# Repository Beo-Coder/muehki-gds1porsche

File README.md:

# Porsche Mü(h)k

### Raspberry Pi Pico powered HID joystick for an old Porsche tractor

# Table of Contents
1. [Features](#features)
2. [Description](#description)
3. [Pinout](#pinout)
4. [Settings](#settings)
   1. [Load Preset](#load-preset)
   2. [Save Preset](#save-preset)
   3. [Modify Preset](#modify-preset)
      1. [General Settings](#general-settings)
      2. [Axes Settings](#axes-settings)
      3. [Button Settings](#button-settings)
  
   4. [Reinit Joystick](#reinit-joystick)
   5. [Reset Preset](#reset-preset)
   6. [Factory Reset](#factory-reset)
   7. [Disable Output](#disable-output)
5. [Notes](#notes)

# Features

- upto 8 analog axes
- upto 24 digital buttons
- fully customizable axes control curves
- fully customizable button behavior
- 10 different config presets
- easy control over rotary controller and LCD
- acts as gamepad or keyboard
- expandable 

# Description

Porsche Mü(h)k is a Raspberry Pi Pico powered controller
to emulate a HI-Device to control various games by using real actuators such as steering wheel,
gas and break pedal of a real tractor/car.
Various actuators can be connected either as analog or digital sensors, like potentiometers and buttons.
It can emulate a gamepad/joystick or a keyboard, depending on which mode is desired.
Each analog axis can operate in one of four different modes, giving full control over the behavior of the axis.

**It may be useful to use an emulator on the host PC to further configure the axes and buttons.**
# Usage

1. Connect all analog and digital actuators according to the pinout guide
2. Connect the Pico to a computer/laptop
3. Load/modify a preset
4. Have fun!

# Pinout

**Note**  
0 = Axis/Button 0 in software.  
If an axis/button is connected to port 2, but in software only two axes/buttons are selected,
the input is not sampled and has no output.

### Analog Headers

<pre> 
            +-----------+
+-----------+-----------+-----------+
|           |           |           |
|     A     |    GND    |    Vcc    |
|           |           |           |
+-----------+-----------+-----------+
</pre>

- A = Analog Input  
- GND = GND
- Vcc = Vcc (3.3V)  

### Digital Headers
<pre>
      +-----------+
+-----------+-----------+
|           |           |
|     S1    |    S2     |
|           |           |
+-----------+-----------+
</pre>

- S1 = Button contact 1
- S2 = Button contact 2

The Button must close or open these two connections.

**More detailed pinout in hardwareReadme**

# Settings

## Load Preset

1. Go to /Settings/Set Preset
2. Select desired preset
3. The Device will reset automatically

## Save Preset

1. Go to /Settings/Save Preset
2. Select desired preset
3. The config is saved to the preset

## Modify Preset

### General Settings
Menu: /Settings/General

- Number of Axes: Select the number of analog inputs/axes (0–8).
- Number of Buttons: Select the number of digital inputs/buttons (0–24).
- Digital Axis Mode: Set the mode for all axes
  - Analog: Axes will be emulated as analog axes (joystick)
  - Analog/Digital: Axes will be emulated as buttons on a joystick (only digital axes)
  - Keyboard: Axes and buttons will be emulated as a keyboard

On Analog/Digital and Keyboard mode, each axis will get two buttons/digital outputs assigned. 
One for an upper limit, one for a lower limit.
In these modes, an axis has only three states: center/off, upper limit, lower limit.

**Important:** After any change of these settings, you have to save the preset and restart the device! [Save Settings](#save-preset), [Reinit Joystick](#reinit-joystick)

### Axes Settings
Menu: /Settings/Axes/{*number of axis*}

- Calibrate: Calibrates the axis
- Base set: Sets the base of the control curve (only in exponential and logarithmic mode)
- Mode: Sets the mode of the axis (linear, exponential, logarithmic, digital)
- Digital Calibration: Calibration for digital mode

#### Calibration
It will calibrate your axis settings.  
Set the minimum position of the axis, this is the position where the output of the axis is the smallest.
Same with the maximum.  
If the center position is not calibrated, the center position is automatically set to the midpoint between minimum and maximum.
If the center is calibrated, one half of the calibration curve can be shorter/longer than the other.

#### Modes
- linear: The curve of the output is linear to the input
- exponential/logarithmic: The curve of the output is exponential/logarithmic to the input (based on base)
- digital: The axis has three states (center/off, upper limit, lower limit) in the general "Analog" mode these will be represented as an analog axis which is either 0, maximum or minimum.

#### Base set
In exponential and logarithmic mode, the base will set the curvature/steepness of the output curve.  
The output curve is split in two halves (base 0 and base 1).
Each base can be set separately, or both bases can be set to the same value.  
Base 0 is the base for the curve between minimum and the center, base 1 for the middle between maximum.  
For exponential curves the value should be greater than 0, for logarithmic curves the value should be smaller than 0.  
If the value is 0, it is linear.  
See also the diagrams below.

#### Digital Calibration
This will select the digital lower and upper limit of the axis.  
Set the position after which the lower/upper output/button should be pressed/set to minimum/maximum.  
All input values that are smaller/greater than the limit will result in the minimum/maximum output value.  
If the input value is between the boarder, no button is pressed (in (general) Analog/Digital or Keyboard mode) or the axis will be 0/center position ((general) Analog Mode).

#### Diagrams
The x-axis represents the input value.
- 0 = center (input) position
- -10 = minimum (input) position
- 10 = maximum (input) position

All of these values can be calibrated with axis calibration.

The y-axis represents the output value (analog mode only)
- 0 = center/0 output
- -10 = minimum (output) value
- 10 = maximum (output) value

Base 0 is the base for the curve between minimum and the center, base 1 for the middle between maximum.

These values will can't be directly controlled.

##### Linear curves:

| Linear axis curve without center calibration                                                                      | Linear axis curve with (different) center calibration                                                                | Linear axis curve with (different) center calibration, different minimum calibration                                      |
|-------------------------------------------------------------------------------------------------------------------|----------------------------------------------------------------------------------------------------------------------|---------------------------------------------------------------------------------------------------------------------------|
|  |  |  |

##### Exponential curves:
| Exponential axis curve without center calibration, same bases                                                          | Exponential axis curve without center calibration, different bases                                                        | Exponential axis curve with (different) center calibration, different bases                                                   |
|------------------------------------------------------------------------------------------------------------------------|---------------------------------------------------------------------------------------------------------------------------|-------------------------------------------------------------------------------------------------------------------------------|
|  |  |  |

##### Logarithmic curves:
| Logarithmic axis curve without center calibration, same bases                                                       | Logarithmic axis curve without center calibration, different bases                                                     | Logarithmic axis curve with (different) center calibration, different bases                                                |
|---------------------------------------------------------------------------------------------------------------------|------------------------------------------------------------------------------------------------------------------------|----------------------------------------------------------------------------------------------------------------------------|
|  |  |  |

##### Other curves (Combinations of all) :
| Exponential half with other half linear (without center calibration)                                                                                 | Exponential half with other half linear, (different) center calibration                                                                                       | Logarithmic half with other half exponential, (different) center calibration                                                                         |
|------------------------------------------------------------------------------------------------------------------------------------------------------|---------------------------------------------------------------------------------------------------------------------------------------------------------------|------------------------------------------------------------------------------------------------------------------------------------------------------|
|  |  |  |

**Note:**
There are many other ways to adjust the curves. See also the Desmos calculator: [Desmos calculator](https://www.desmos.com/calculator/y6jawpiyea)  
Note that the values of the Desmos calculator do not match those of the device.

### Button Settings

Menu: /Settings/Buttons/{*number of button*}

- Mode: Whether the button should behave as (temporary) button or as (toggle) button
- Type: Whether the button is NO (normally open) or NC (normally closed)

#### Mode
- Button: Button behaves as a button. There is only an output when the button is pressed.
- Toggle: Button behaves as a toggle button. Ont the first press the output goes high/1, the next press sets the output to 0/low.

#### Type
- Normally Open
- Normally Closed

Whether the button opens or closes on a press.

**Important:**
Axes and button settings are adapted immediately.
To keep them after the joystick is reloaded or turned off the settings must be saved. [Save Settings](#save-preset)  
There is no need to reinit the joystick after axes or button settings have changed.

## Reinit Joystick

This option reloads the joystick. 
All settings that are not saved will be lost.

## Reset Preset

The current selected preset will be set to factory settings.
After that, the joystick will be reloaded.

## Factory Reset

All settings (all presets) are set back to factory settings.
After that, the joystick will be reloaded.

## Disable Output
This setting disables the output of the computer.  
Especially useful in Keyboard mode.  
Press it again to enable the output again.

# Notes
The configuration/device can be tested on gamepad/joystick test websites/software.  
Example website I used for testing: [Gamepad tester](https://hardwaretester.com/gamepad)

More detailed hardware/software guides are under [READMEhardware](READMEhardware.md)/[READMEsoftware](READMEsoftware.md)  
There are also the board dimensions as well as the schematic/gerber files.

There are no settings stored on the Pico. So the Pico can also be used for other projects.

If there are any bugs/problems, or you have any questions, please contact me.

Mühk or Mük is are the same things. :)

( ._.)

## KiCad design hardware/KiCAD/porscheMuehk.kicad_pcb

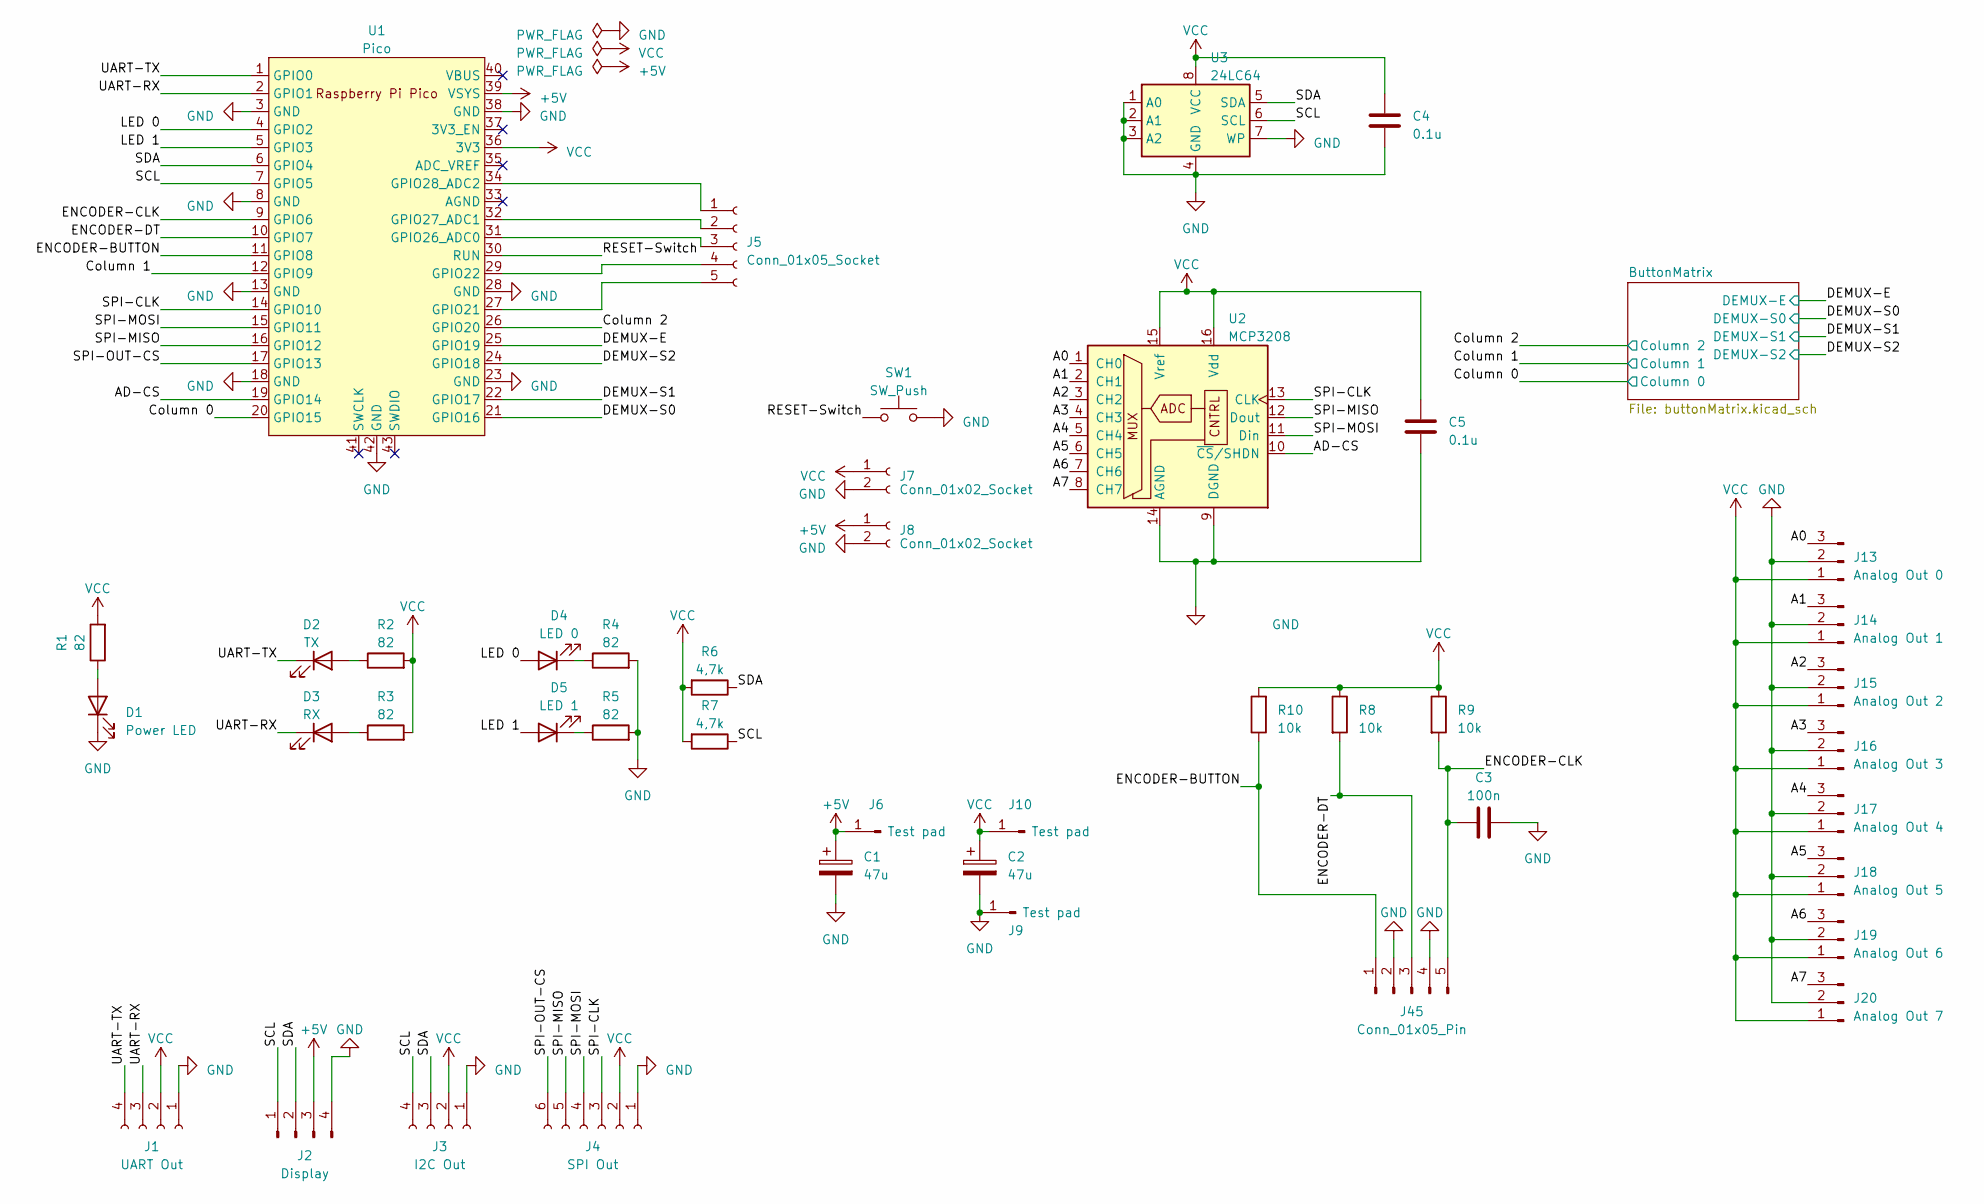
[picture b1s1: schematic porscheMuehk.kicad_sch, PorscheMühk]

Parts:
C1, C2: 47u; CP_Elec_5x5.3
C3: 100n; C_0805_2012Metric_Pad1.18x1.45mm_HandSolder
C4, C5: 0.1u; C_0805_2012Metric_Pad1.18x1.45mm_HandSolder
D1: Power LED; LED_0805_2012Metric_Pad1.15x1.40mm_HandSolder
D2: TX; LED_0805_2012Metric_Pad1.15x1.40mm_HandSolder
D3: RX; LED_0805_2012Metric_Pad1.15x1.40mm_HandSolder
D4: LED 0; LED_0805_2012Metric_Pad1.15x1.40mm_HandSolder
D5: LED 1; LED_0805_2012Metric_Pad1.15x1.40mm_HandSolder
J1: UART Out; PinSocket_1x04_P2.54mm_Vertical
J2: Display; Molex_KK-254_AE-6410-04A_1x04_P2.54mm_Vertical
J3: I2C Out; PinSocket_1x04_P2.54mm_Vertical
J4: SPI Out; PinSocket_1x06_P2.54mm_Vertical
J5: Conn_01x05_Socket; PinSocket_1x05_P2.54mm_Vertical
J6, J9, J10: Test pad; TestPoint_Pad_1.5x1.5mm
J7, J8: Conn_01x02_Socket; PinSocket_1x02_P2.54mm_Vertical
J13: Analog Out 0; Molex_KK-254_AE-6410-03A_1x03_P2.54mm_Vertical
J14: Analog Out 1; Molex_KK-254_AE-6410-03A_1x03_P2.54mm_Vertical
J15: Analog Out 2; Molex_KK-254_AE-6410-03A_1x03_P2.54mm_Vertical
J16: Analog Out 3; Molex_KK-254_AE-6410-03A_1x03_P2.54mm_Vertical
J17: Analog Out 4; Molex_KK-254_AE-6410-03A_1x03_P2.54mm_Vertical
J18: Analog Out 5; Molex_KK-254_AE-6410-03A_1x03_P2.54mm_Vertical
J19: Analog Out 6; Molex_KK-254_AE-6410-03A_1x03_P2.54mm_Vertical
J20: Analog Out 7; Molex_KK-254_AE-6410-03A_1x03_P2.54mm_Vertical
J45: Conn_01x05_Pin; Molex_KK-254_AE-6410-05A_1x05_P2.54mm_Vertical
R1, R2, R3, R4, R5: 82; R_0805_2012Metric_Pad1.20x1.40mm_HandSolder
R6, R7: 4,7k; R_0805_2012Metric_Pad1.20x1.40mm_HandSolder
R8, R9, R10: 10k; R_0805_2012Metric_Pad1.20x1.40mm_HandSolder
SW1: SW_Push; SW_Push_1P1T_NO_6x6mm_H9.5mm
U1: Pico; RPi_Pico_SMD_TH
U2: MCP3208; SOIC-16_3.9x9.9mm_P1.27mm
U3: 24LC64; SOIC-8_3.9x4.9mm_P1.27mm

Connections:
+5V: C1.1, J2.3, J6.1, J8.1, U1.39 (VSYS)
/A0: J13.3, U2.1 (CH0)
/A1: J14.3, U2.2 (CH1)
/A2: J15.3, U2.3 (CH2)
/A3: J16.3, U2.4 (CH3)
/A4: J17.3, U2.5 (CH4)
/A5: J18.3, U2.6 (CH5)
/A6: J19.3, U2.7 (CH6)
/A7: J20.3, U2.8 (CH7)
/AD-CS: U1.19 (GPIO14), U2.10 (~CS/SHDN)
/Column 0: U1.20 (GPIO15); also elsewhere on the board
/Column 1: U1.12 (GPIO9); also elsewhere on the board
/Column 2: U1.26 (GPIO20); also elsewhere on the board
/DEMUX-E: U1.25 (GPIO19); also elsewhere on the board
/DEMUX-S0: U1.21 (GPIO16); also elsewhere on the board
/DEMUX-S1: U1.22 (GPIO17); also elsewhere on the board
/DEMUX-S2: U1.24 (GPIO18); also elsewhere on the board
/ENCODER-BUTTON: J45.1, R10.1, U1.11 (GPIO8)
/ENCODER-DT: J45.3, R8.2, U1.10 (GPIO7)
/LED 0: D4.2 (A), U1.4 (GPIO2)
/LED 1: D5.2 (A), U1.5 (GPIO3)
/RESET-Switch: SW1.1, U1.30 (RUN)
/SCL: J2.1, J3.4, R7.1, U1.7 (GPIO5), U3.6 (SCL)
/SDA: J2.2, J3.3, R6.1, U1.6 (GPIO4), U3.5 (SDA)
/SPI-CLK: J4.3, U1.14 (GPIO10), U2.13 (CLK)
/SPI-MISO: J4.5, U1.16 (GPIO12), U2.12 (Dout)
/SPI-MOSI: J4.4, U1.15 (GPIO11), U2.11 (Din)
/SPI-OUT-CS: J4.6, U1.17 (GPIO13)
/UART-RX: D3.1 (K), J1.3, U1.2 (GPIO1)
/UART-TX: D2.1 (K), J1.4, U1.1 (GPIO0)
unnamed: D1.2 (A), R1.1
unnamed: D2.2 (A), R2.1
unnamed: D3.2 (A), R3.1
unnamed: D4.1 (K), R4.1
unnamed: D5.1 (K), R5.1
unnamed: J5.1, U1.34 (GPIO28_ADC2)
unnamed: J5.2, U1.32 (GPIO27_ADC1)
unnamed: J5.3, U1.31 (GPIO26_ADC0)
unnamed: J5.4, U1.29 (GPIO22)
unnamed: J5.5, U1.27 (GPIO21)
VCC: C2.1, C4.1, C5.1, J1.2, J3.2, J4.2, J7.1, J10.1, J13.1, J14.1, J15.1, J16.1, J17.1, J18.1, J19.1, J20.1, R1.2, R2.2, R3.2, R6.2, R7.2, R8.1, R9.1, R10.2, U1.36 (3V3), U2.15 (Vref), U2.16 (Vdd), U3.8 (VCC); also elsewhere on the board

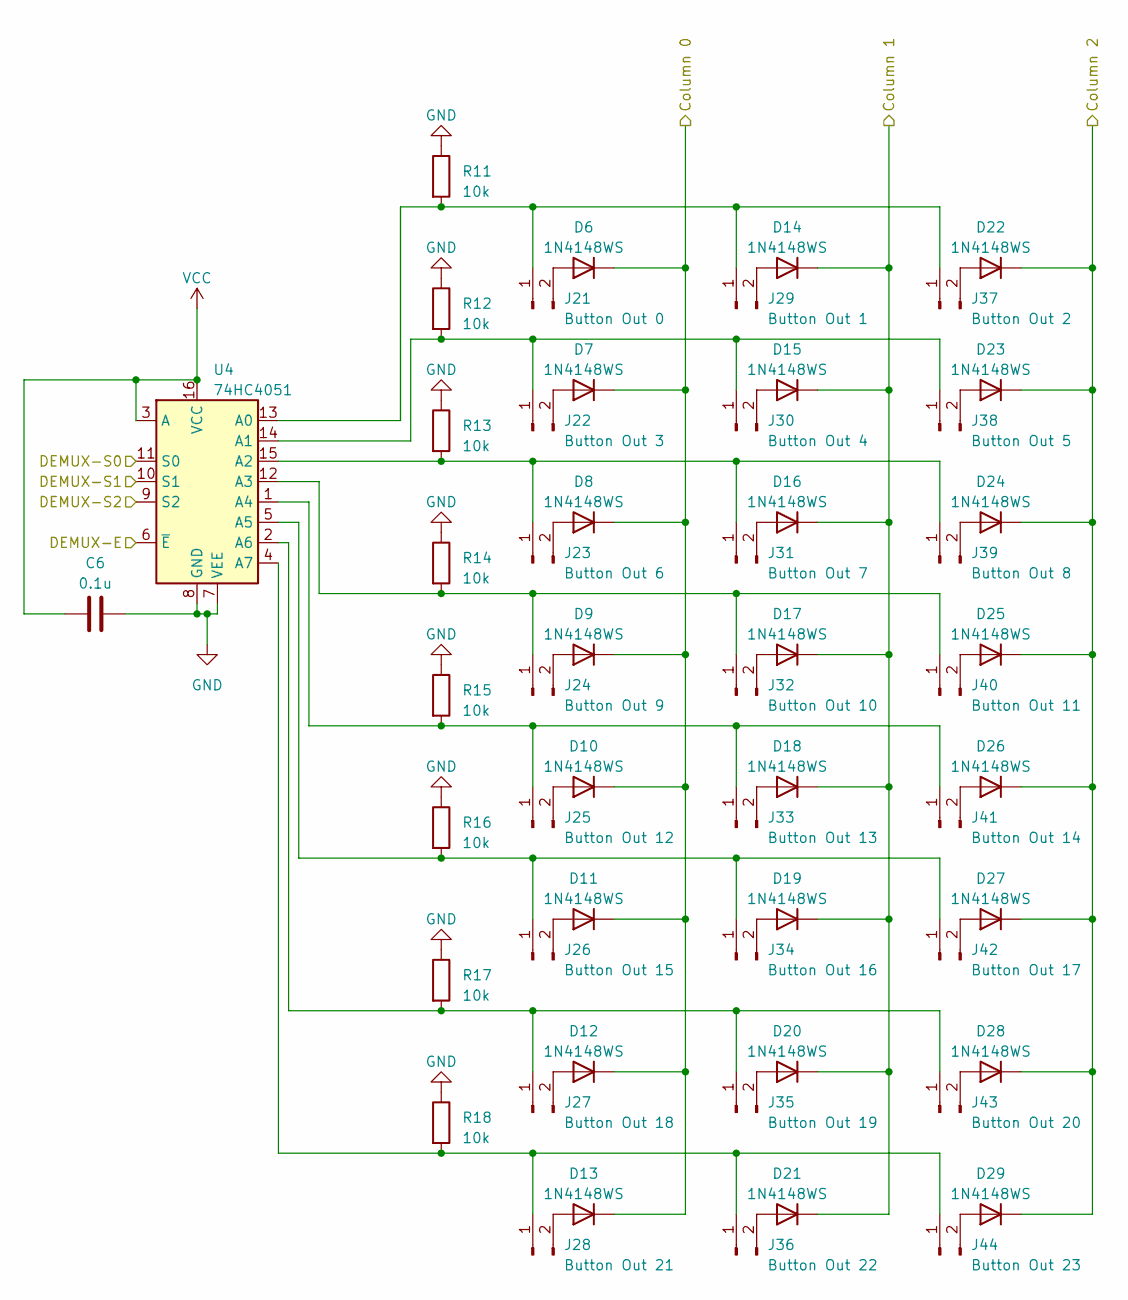
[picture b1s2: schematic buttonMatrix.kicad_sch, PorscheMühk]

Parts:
C6: 0.1u; C_0805_2012Metric_Pad1.18x1.45mm_HandSolder
D6, D7, D8, D9, D10, D11, D12, D13, D14, D15, D16, D17, D18, D19, D20, D21, D22, D23, D24, D25, D26, D27, D28, D29: 1N4148WS; D_SOD-323_HandSoldering
J21: Button Out 0; Molex_KK-254_AE-6410-02A_1x02_P2.54mm_Vertical
J22: Button Out 3; Molex_KK-254_AE-6410-02A_1x02_P2.54mm_Vertical
J23: Button Out 6; Molex_KK-254_AE-6410-02A_1x02_P2.54mm_Vertical
J24: Button Out 9; Molex_KK-254_AE-6410-02A_1x02_P2.54mm_Vertical
J25: Button Out 12; Molex_KK-254_AE-6410-02A_1x02_P2.54mm_Vertical
J26: Button Out 15; Molex_KK-254_AE-6410-02A_1x02_P2.54mm_Vertical
J27: Button Out 18; Molex_KK-254_AE-6410-02A_1x02_P2.54mm_Vertical
J28: Button Out 21; Molex_KK-254_AE-6410-02A_1x02_P2.54mm_Vertical
J29: Button Out 1; Molex_KK-254_AE-6410-02A_1x02_P2.54mm_Vertical
J30: Button Out 4; Molex_KK-254_AE-6410-02A_1x02_P2.54mm_Vertical
J31: Button Out 7; Molex_KK-254_AE-6410-02A_1x02_P2.54mm_Vertical
J32: Button Out 10; Molex_KK-254_AE-6410-02A_1x02_P2.54mm_Vertical
J33: Button Out 13; Molex_KK-254_AE-6410-02A_1x02_P2.54mm_Vertical
J34: Button Out 16; Molex_KK-254_AE-6410-02A_1x02_P2.54mm_Vertical
J35: Button Out 19; Molex_KK-254_AE-6410-02A_1x02_P2.54mm_Vertical
J36: Button Out 22; Molex_KK-254_AE-6410-02A_1x02_P2.54mm_Vertical
J37: Button Out 2; Molex_KK-254_AE-6410-02A_1x02_P2.54mm_Vertical
J38: Button Out 5; Molex_KK-254_AE-6410-02A_1x02_P2.54mm_Vertical
J39: Button Out 8; Molex_KK-254_AE-6410-02A_1x02_P2.54mm_Vertical
J40: Button Out 11; Molex_KK-254_AE-6410-02A_1x02_P2.54mm_Vertical
J41: Button Out 14; Molex_KK-254_AE-6410-02A_1x02_P2.54mm_Vertical
J42: Button Out 17; Molex_KK-254_AE-6410-02A_1x02_P2.54mm_Vertical
J43: Button Out 20; Molex_KK-254_AE-6410-02A_1x02_P2.54mm_Vertical
J44: Button Out 23; Molex_KK-254_AE-6410-02A_1x02_P2.54mm_Vertical
R11, R12, R13, R14, R15, R16, R17, R18: 10k; R_0805_2012Metric_Pad1.20x1.40mm_HandSolder
U4: 74HC4051; SO-16_3.9x9.9mm_P1.27mm

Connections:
/Column 0: D6.1 (K), D7.1 (K), D8.1 (K), D9.1 (K), D10.1 (K), D11.1 (K), D12.1 (K), D13.1 (K); also elsewhere on the board
/Column 1: D14.1 (K), D15.1 (K), D16.1 (K), D17.1 (K), D18.1 (K), D19.1 (K), D20.1 (K), D21.1 (K); also elsewhere on the board
/Column 2: D22.1 (K), D23.1 (K), D24.1 (K), D25.1 (K), D26.1 (K), D27.1 (K), D28.1 (K), D29.1 (K); also elsewhere on the board
/DEMUX-E: U4.6 (~E); also elsewhere on the board
/DEMUX-S0: U4.11 (S0); also elsewhere on the board
/DEMUX-S1: U4.10 (S1); also elsewhere on the board
/DEMUX-S2: U4.9 (S2); also elsewhere on the board
unnamed: D6.2 (A), J21.2
unnamed: D7.2 (A), J22.2
unnamed: D8.2 (A), J23.2
unnamed: D9.2 (A), J24.2
unnamed: D10.2 (A), J25.2
unnamed: D11.2 (A), J26.2
unnamed: D12.2 (A), J27.2
unnamed: D13.2 (A), J28.2
unnamed: D14.2 (A), J29.2
unnamed: D15.2 (A), J30.2
unnamed: D16.2 (A), J31.2
unnamed: D17.2 (A), J32.2
unnamed: D18.2 (A), J33.2
unnamed: D19.2 (A), J34.2
unnamed: D20.2 (A), J35.2
unnamed: D21.2 (A), J36.2
unnamed: D22.2 (A), J37.2
unnamed: D23.2 (A), J38.2
unnamed: D24.2 (A), J39.2
unnamed: D25.2 (A), J40.2
unnamed: D26.2 (A), J41.2
unnamed: D27.2 (A), J42.2
unnamed: D28.2 (A), J43.2
unnamed: D29.2 (A), J44.2
unnamed: J21.1, J29.1, J37.1, R11.2, U4.13 (A0)
unnamed: J22.1, J30.1, J38.1, R12.2, U4.14 (A1)
unnamed: J23.1, J31.1, J39.1, R13.2, U4.15 (A2)
unnamed: J24.1, J32.1, J40.1, R14.2, U4.12 (A3)
unnamed: J25.1, J33.1, J41.1, R15.2, U4.1 (A4)
unnamed: J26.1, J34.1, J42.1, R16.2, U4.5 (A5)
unnamed: J27.1, J35.1, J43.1, R17.2, U4.2 (A6)
unnamed: J28.1, J36.1, J44.1, R18.2, U4.4 (A7)
VCC: C6.1, U4.3 (A), U4.16 (VCC); also elsewhere on the board

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
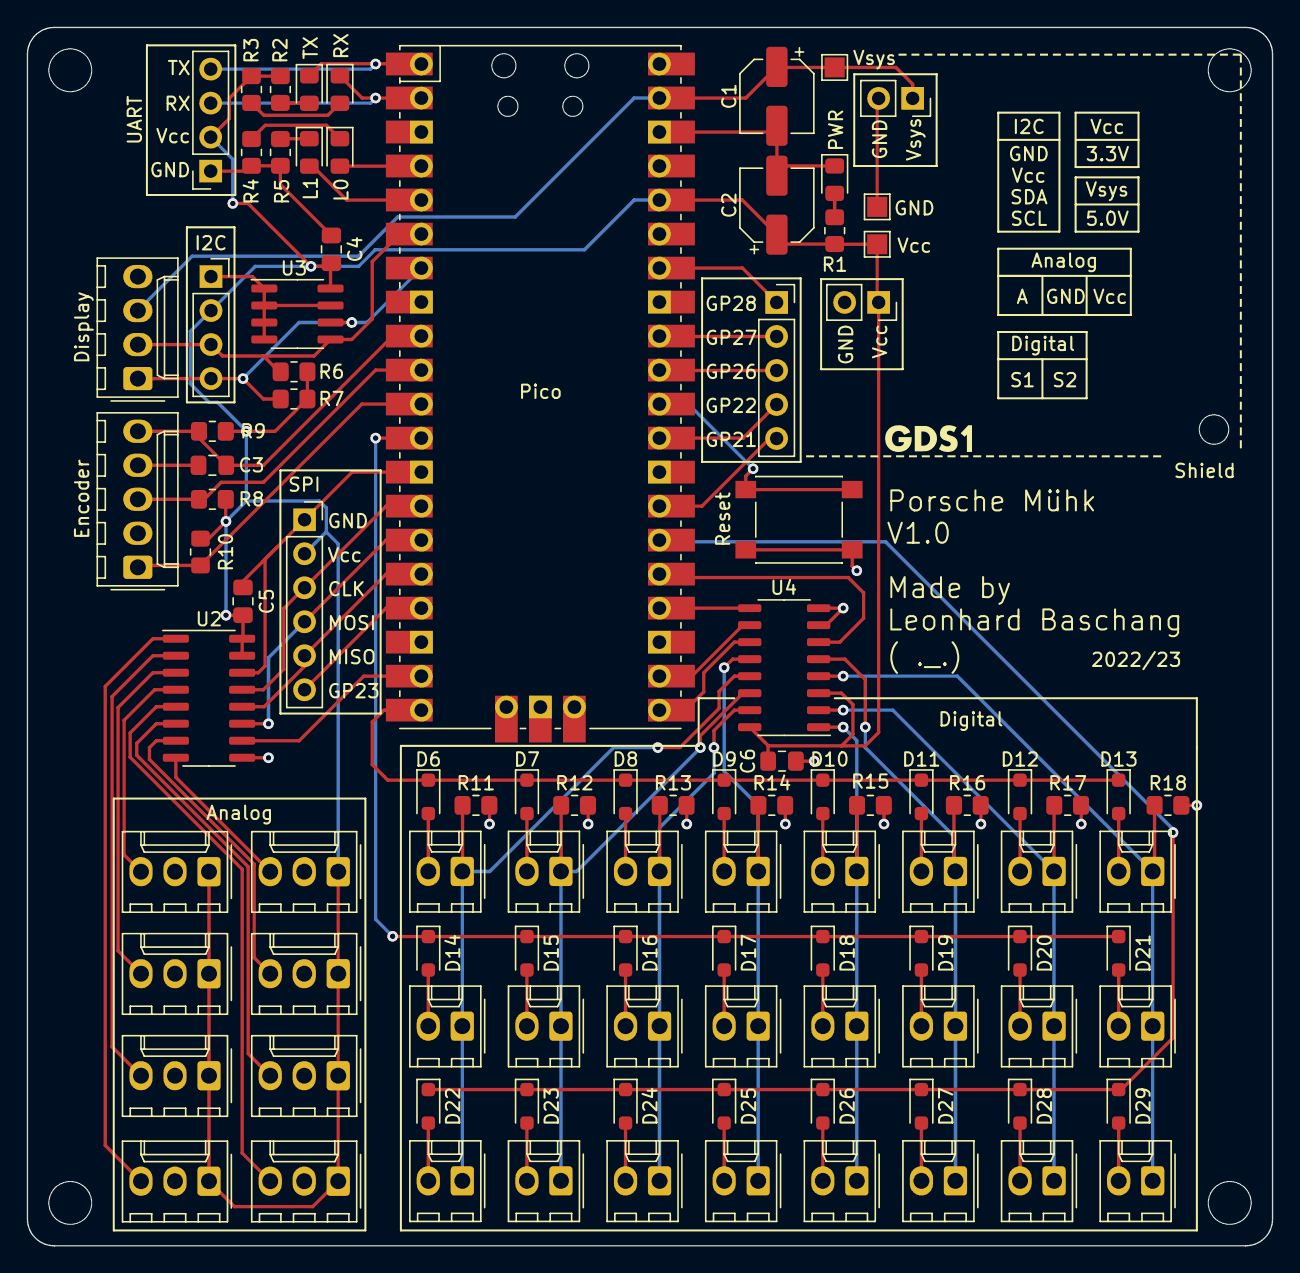
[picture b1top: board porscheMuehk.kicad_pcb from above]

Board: 2 copper layers, 93.0 x 91.0 mm, 101 parts (0 on the bottom side), 75 nets.

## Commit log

2023-06-05 First commit with V2
2023-06-10 Changed a lot (a lot)
2023-06-10 Changed a lot^2 (a lot^2)
2023-09-30 added README and fixed some bugs. Removed Libs and added them to .ini file
2023-10-01 changed some images and fixed typos
2023-10-01 changed some images
2023-12-06 changed direction of encoder
2023-12-06 updated README.md and updated startup screen
2023-12-09 fixed issue where device reinit even if it shouldn't
2023-12-10 other (better) expo and log mode. Also fixed bugs with lin, expo and log modes on axes
2023-12-10 fixed lcd auto backlight off
2023-12-10 changed some graphs and calculator
2023-12-10 even better log/expo mode
2024-05-29 Changed some things. Added more hardware details
2024-05-29 Added update interval
2024-05-29 Fixed update interval
2024-07-09 Fixed Output LCD line
2024-07-09 encoder button debounce
2024-07-09 fixed analog/digital mode
2024-07-09 Better debounce time
